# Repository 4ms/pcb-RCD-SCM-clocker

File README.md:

# PCB for RCD and SCM eurorack modules #

## Rotating Clock Divider, and Shuffling Clock Multiplier ##

### Pre-built versions (PCB v1.2) and Kit version (PCB v1.0.x) ###

This repository is an archive for the kit and pre-built versions of the RCD and SCM.

While we believe these files are accurate, there may be minor variations and/or corrections made during assembly that aren't recorded in these files.

Copyright (c) 2010, 2011, 2014, 2020 Dan Green (danngreen1@gmail.com)

Licensed by the [CC BY-NC-SA license](https://creativecommons.org/licenses/by-nc-sa/4.0/) (Creative Commons, Attribution, NonCommercial, ShareAlike).

Please read the above license carefully and contact us if you have any questions regarding acceptable use of these files.

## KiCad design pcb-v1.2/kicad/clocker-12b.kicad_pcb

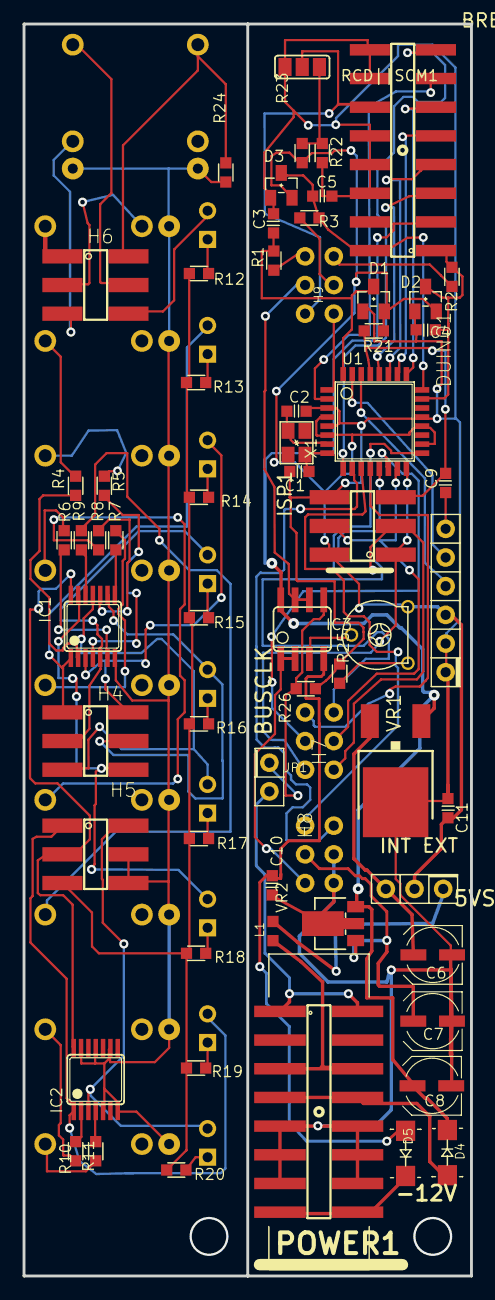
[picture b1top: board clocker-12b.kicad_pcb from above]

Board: 16 copper layers, 39.6 x 110.9 mm, 84 parts (0 on the bottom side), 87 nets.

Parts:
5VSEL1: HEADER-1X3-TH
'DUINO1: HEADER-1X6-TH
BREAKOUT1: HEADER-2x8-SMT; HEADER-2X8-SMT
C1, C2: 9pF; C0603
C3, C4, C5: 330pF; C0603
C6, C7, C8: 47uF; C-POL-5
C9, C10, C11: 0.1uF; C0603
D1, D2, D3: BAT54S; SOT23
D4, D5: B140-E3; SMA
H4, H5, H6: HEADER-2X3-B2B-MALESMT; HEADER-2X3-SMT
H7, H8, H9: HEADER-2X3-B2B-FEMALETH-BOT; HEADER-2X3-TH-BOTTOM
IC1, IC2: 40106BPWR; TSSOP14
IC3: TL072; SOIC8
ISP1: HEADER-2X3-SMT
J1-CLK-IN1, J2-OUT1, J3-OUT2, J4-OUT3, J5-OUT4, J6-OUT5, J7-OUT6, J8-OUT7, J9-OUT8, J10-ROTATE1, J11-RST-SLP1: PJ301M-12
JP1: 1x2-TH; HEADER-1X2-TH
L1: BEAD; 0603
LED1: White; LED-T1
LED2: Blue; LED-T1
LED3, LED9: Red or blue; LED-T1
LED4, LED7: Green; LED-T1
LED5: Red or green; LED-T1
LED6, LED8: Blue or green; LED-T1
POWER1: HEADER-2X8-SMT; HEADER-2X8-SMT-SHROUDED
R1, R2, R3: 470; R0603
R4, R5, R6, R7, R8, R9, R10, R11: 1k; R0603
R12, R13, R14, R15, R16, R17, R18, R19, R20, R21, R25: 10k; R0603
R22, R23, R24, R26: 470k; R0603
RCD||SCM1: solder-blob; SJ_2
TR24: 10k; PIHER-6MM
U1: ATMEGA328; TQFP-32
VR1: 78M05; DPAK
VR2: 78L09; SOT89
X1: 16MHz; FA-238

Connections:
+5V: 5VSEL1.P$2, 'DUINO1.P$3, C11.2, D1.2, D2.2, D3.2, ISP1.2, R21.1, R23.2, TR24.3, U1.4, U1.6, U1.18, U1.20
+9V: H5.3, IC1.14, IC2.14
+12V: BREAKOUT1.3, C8.+, D4.K, IC3.8, VR1.1, VR2.3
+VREF: H5.5, R12.2, R13.2, R14.2, R15.2, R16.2, R17.2, R18.2, R19.2, R20.2
/clocker-12b_1/CV1: BREAKOUT1.1, C4.1, D2.3, R2.2, U1.23
/clocker-12b_1/CV2: BREAKOUT1.2, C5.1, D3.3, R3.2, U1.24
/clocker-12b_1/FAST|COUNT: BREAKOUT1.15, U1.9
/clocker-12b_1/MISO: H7.P$5, ISP1.1, U1.16
/clocker-12b_1/MOSI: H7.P$4, ISP1.4, U1.15
/clocker-12b_1/MUTE|GATE: BREAKOUT1.13, U1.2
/clocker-12b_1/PW|DIV32: BREAKOUT1.11, U1.25
/clocker-12b_1/RESET: C9.2, ISP1.5, R21.2, U1.29
/clocker-12b_1/SCK: H7.P$6, ISP1.3, U1.17
/clocker-12b_1/SHFL|RESET: BREAKOUT1.5, U1.28
/clocker-12b_1/SKIP|DIV16: BREAKOUT1.9, U1.26
/clocker-12b_1/SYNC|SPREAD: BREAKOUT1.7, U1.27
/clocker-12b_2/-12V: D5.K, POWER1.15, POWER1.16
AGND: H5.4, H5.6, IC1.7, IC2.5, IC2.7, IC2.9, IC2.11, IC2.13, J1-CLK-IN1.2, J2-OUT1.2, J3-OUT2.2, J4-OUT3.2, J5-OUT4.2, J6-OUT5.2, J7-OUT6.2, J8-OUT7.2, J9-OUT8.2, J10-ROTATE1.2, J11-RST-SLP1.2, R24.2
GND: 'DUINO1.P$1, 'DUINO1.P$2, BREAKOUT1.6, BREAKOUT1.8, BREAKOUT1.10, BREAKOUT1.14, BREAKOUT1.16, C1.2, C2.2, C3.2, C4.2, C5.2, C6.-, C7.-, C8.-, C10.1, C11.1, D1.1, D2.1, D3.1, H8.P$4, H8.P$6, ISP1.6, POWER1.9, POWER1.10, POWER1.11, POWER1.12, POWER1.13, POWER1.14, R22.1, R25.2, R26.2, RCD||SCM1.3, U1.3, U1.5, U1.21, VR1.4, VR2.2A, VR2.2B
IN-SW: H9.P$3, IC3.6, IC3.7
unnamed: 5VSEL1.P$1, L1.2
unnamed: 5VSEL1.P$3, C6.+, VR1.3
unnamed: 'DUINO1.P$4, U1.30
unnamed: 'DUINO1.P$5, U1.31
unnamed: 'DUINO1.P$6, C9.1
unnamed: BREAKOUT1.12, H9.P$5, RCD||SCM1.2
unnamed: C1.1, U1.8, X1.3
unnamed: C2.1, U1.7, X1.1
unnamed: C3.1, D1.3, R1.2, U1.32
unnamed: C7.+, H8.P$3, VR2.1
unnamed: C10.2, D5.A, IC3.4
unnamed: D4.A, POWER1.7, POWER1.8
unnamed: H4.1, IC1.1, LED2.K
unnamed: H4.2, IC1.3, LED3.K
unnamed: H4.3, IC1.5, LED4.K
unnamed: H4.4, IC1.9, LED5.K
unnamed: H4.5, IC1.11, LED6.K
unnamed: H4.6, IC1.13, LED7.K
unnamed: H5.1, IC2.1, LED8.K
unnamed: H5.2, IC2.3, LED9.K
unnamed: H6.1, J1-CLK-IN1.1
unnamed: H6.2, J10-ROTATE1.1, R24.1
unnamed: H6.3, J1-CLK-IN1.3
unnamed: H6.4, J11-RST-SLP1.1
unnamed: H6.5, J11-RST-SLP1.3
unnamed: H6.6, LED1.K
unnamed: H7.P$1, U1.12
unnamed: H7.P$2, U1.13
unnamed: H7.P$3, U1.14
unnamed: H8.P$1, U1.11
unnamed: H8.P$2, U1.10
unnamed: H8.P$5, IC3.1, IC3.2
unnamed: H9.P$1, R1.1
unnamed: H9.P$2, R2.1
unnamed: H9.P$4, R3.1
unnamed: H9.P$6, U1.1
unnamed: IC1.2, R4.1
unnamed: IC1.4, R5.1
unnamed: IC1.6, R6.1
unnamed: IC1.8, R7.1
unnamed: IC1.10, R8.1
unnamed: IC1.12, R9.1
unnamed: IC2.2, R10.1
unnamed: IC2.4, R11.1
unnamed: IC3.3, TR24.2
unnamed: IC3.5, JP1.P$1, R26.1
unnamed: J2-OUT1.1, R4.2
unnamed: J3-OUT2.1, R5.2
unnamed: J4-OUT3.1, R6.2
unnamed: J5-OUT4.1, R7.2
unnamed: J6-OUT5.1, R8.2
unnamed: J7-OUT6.1, R9.2
unnamed: J8-OUT7.1, R10.2
unnamed: J9-OUT8.1, R11.2
unnamed: JP1.P$2, POWER1.1, POWER1.2
unnamed: L1.1, POWER1.5, POWER1.6
unnamed: LED1.A, R12.1
unnamed: LED2.A, R13.1
unnamed: LED3.A, R14.1
unnamed: LED4.A, R15.1
unnamed: LED5.A, R16.1
unnamed: LED6.A, R17.1
unnamed: LED7.A, R18.1
unnamed: LED8.A, R19.1
unnamed: LED9.A, R20.1
unnamed: R22.2, R23.1, RCD||SCM1.1
unnamed: R25.1, TR24.1

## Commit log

2020-09-07 Added PCB v1.2 Eagle and Kicad projects; PCB 1.0.4d gEDA project
2020-09-07 Added README
